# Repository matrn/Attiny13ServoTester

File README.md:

Attiny13 Servo Tester
==========

Servo tester using cheap attiny13.

## Code

Code is written in arduino language. Use Arduino IDE to `Attiny13ServoTester.ino` into your MCU.

## Schematic & PCB

Schematic and PCB are created using kicad. All files necessary for kicad are stored in `kicad` directory.

## Modes

Tester has multiple modes:

 - **Potentiometer mode** - servo position is controlled by potentiometer and leds `LED_MIN` and `LED_MAX` light up when minimal or maximal position is reached.
 - **Auto mode** - servo tester sets up position automatically from 0° to 180° and from 180° to 0°.
 - **90° mode** - position is whole time at 90°

## Arduino IDE settings

 * Board: ATtiny13
 * Brown-out Detection Level: "1.8V"
 * Link Time Optimalisation: "LTO Enabled"
 * Processor Version: "ATtiny13"
 * Processor Speed: "9.6MHz Internal Oscillator"
 * Programmer: "Arduino as ISP"

## Additional notes

 - Because servo can create current impact it's better to add electrolytic and ceramic capacitor paraller to power.
 - It's necessary to mirror SMD components on kicad PCB because PCB also contains THT components.

## ToDo

 - [ ] mirror SMD elements
 - [x] add resistor for servo
 - [x] complete all modes
 - [x] add mode change led signalisation
 - [x] cleanup code

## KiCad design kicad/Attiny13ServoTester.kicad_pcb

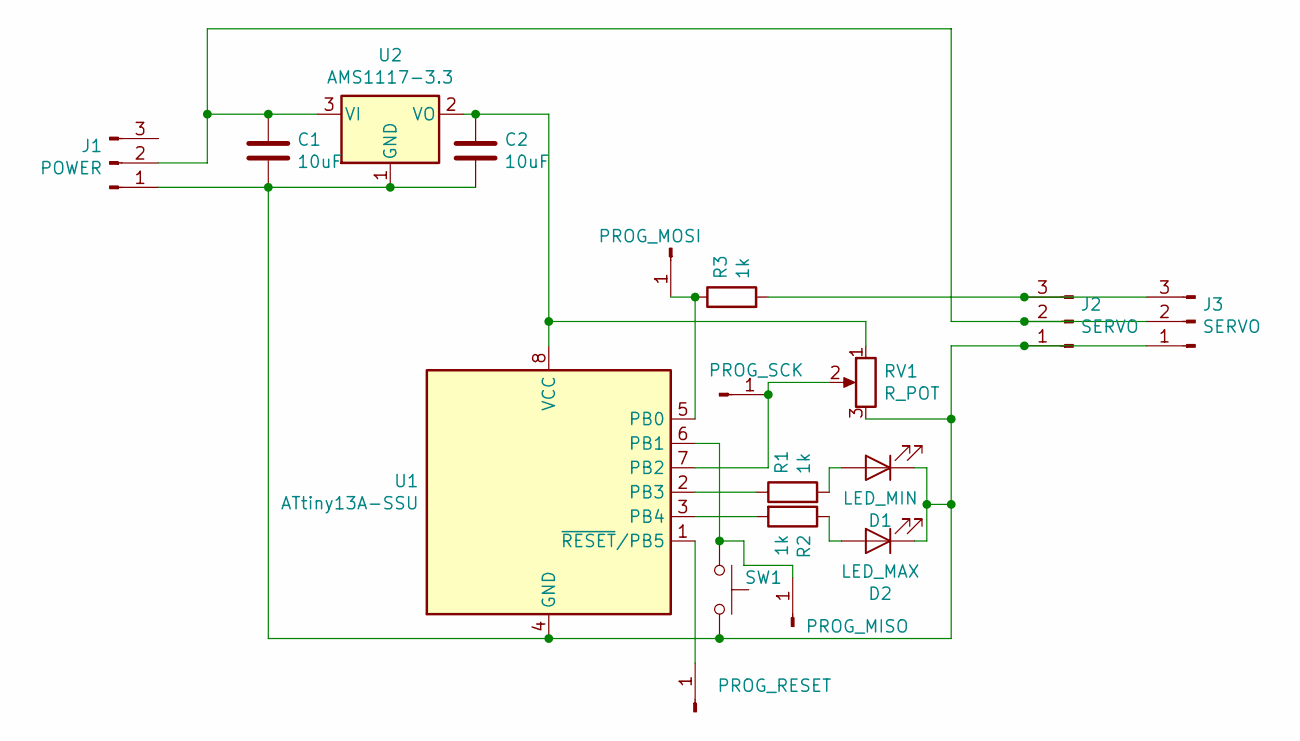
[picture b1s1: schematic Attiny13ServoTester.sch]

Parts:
C1, C2: 10uF; C_0805_2012Metric_Pad1.15x1.40mm_HandSolder
D1: LED_MIN; LED_0603_1608Metric
D2: LED_MAX; LED_0603_1608Metric
J1: POWER; PinHeader_1x03_P2.54mm_Vertical
J2, J3: SERVO; PinHeader_1x03_P2.54mm_Vertical
J4: PROG_SCK; Pin_D0.7mm_L6.5mm_W1.8mm_FlatFork
J5: PROG_MOSI; Pin_D0.7mm_L6.5mm_W1.8mm_FlatFork
J6: PROG_RESET; Pin_D0.7mm_L6.5mm_W1.8mm_FlatFork
J7: PROG_MISO; Pin_D0.7mm_L6.5mm_W1.8mm_FlatFork
R1, R2, R3: 1k; R_0603_1608Metric_Pad1.05x0.95mm_HandSolder
RV1: R_POT; Potentiometer_Alps_RK09K_Single_Vertical
SW1: SW_Push; SW_PUSH_6mm
U1: ATtiny13A-SSU; SOIC-8_3.9x4.9mm_P1.27mm
U2: AMS1117-3.3; SOT-223-3_TabPin2

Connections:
unnamed: C1.1, J1.2, J2.2, J3.2, U2.3 (VI)
unnamed: C1.2, C2.1, D1.1 (K), D2.1 (K), J1.1, J2.1, J3.1, RV1.3, SW1.2, U1.4 (GND), U2.1 (GND)
unnamed: C2.2, RV1.1, U1.8 (VCC), U2.2 (VO)
unnamed: D1.2 (A), R1.2
unnamed: D2.2 (A), R2.1
unnamed: J2.3, J3.3, R3.2
unnamed: J4.1, RV1.2, U1.7 (PB2)
unnamed: J5.1, R3.1, U1.5 (PB0)
unnamed: J6.1, U1.1 (~RESET~/PB5)
unnamed: J7.1, SW1.1, U1.6 (PB1)
unnamed: R1.1, U1.2 (PB3)
unnamed: R2.2, U1.3 (PB4)

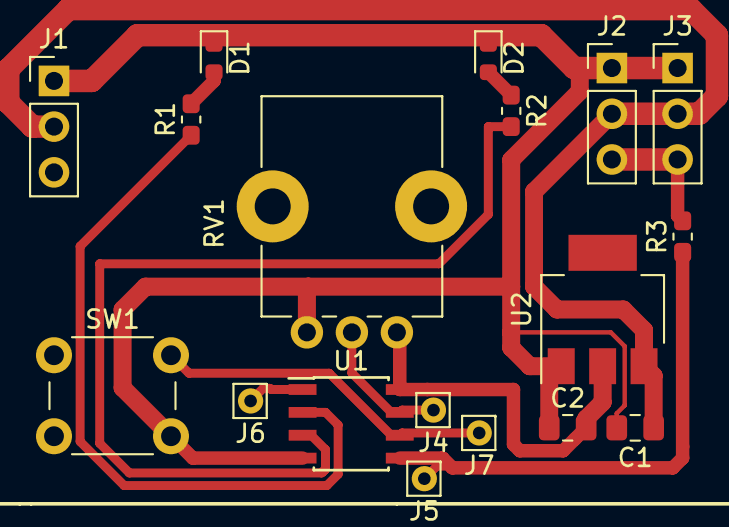
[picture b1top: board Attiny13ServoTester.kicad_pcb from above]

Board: 2 copper layers, 18 parts (0 on the bottom side), 12 nets.

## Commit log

2019-01-24 new files
2019-01-28 work in progress
2019-02-17 pcb update
2019-03-16 add point to README
2019-03-28 kicad useful remove
2019-04-26 finishing project
2019-04-26 fixed inverted potentiometer
2019-08-17 Create LICENSE
